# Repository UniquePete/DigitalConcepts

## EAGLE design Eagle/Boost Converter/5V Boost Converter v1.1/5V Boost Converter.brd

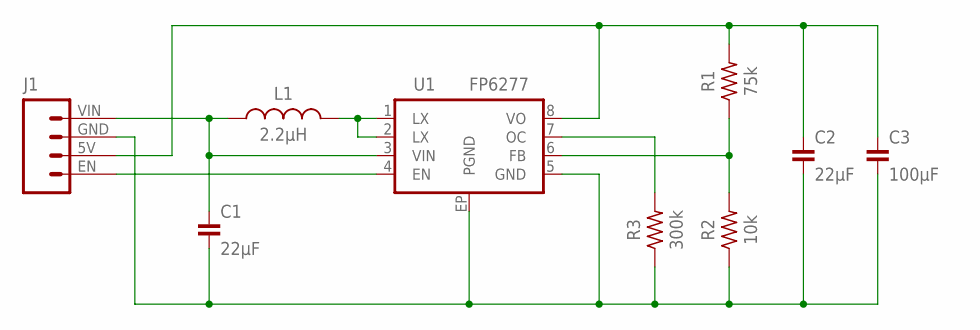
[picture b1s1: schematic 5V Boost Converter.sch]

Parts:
C1, C2: 22µF; C0805
C3: 100µF; C1206
J1: HEADER-1X4-FP6277; CONN_04-FP6277
L1: 2.2µH; L1008
R1: 75k; R0805
R2: 10k; R0805
R3: 300k; R0805
U1: FP6277; SOP-8(EP)

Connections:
5V: C2.1, C3.1, J1.5V (2), R1.2, U1.8 (VO)
EN: J1.EN (1), U1.4 (EN)
GND: C1.2, C2.2, C3.2, J1.GND (3), R2.1, R3.1, U1.5 (GND), U1.EP (PGND)
unnamed: L1.P$1 (1), U1.1 (LX), U1.2 (LX)
unnamed: R1.1, R2.2, U1.6 (FB)
unnamed: R3.2, U1.7 (OC)
VIN: C1.1, J1.VIN (4), L1.P$2 (2), U1.3 (VIN)

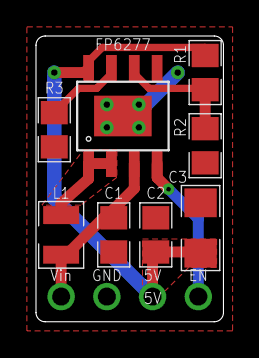
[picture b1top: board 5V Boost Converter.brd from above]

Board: 2 copper layers, 10.4 x 15.9 mm, 9 parts (1 on the bottom side), 7 nets.

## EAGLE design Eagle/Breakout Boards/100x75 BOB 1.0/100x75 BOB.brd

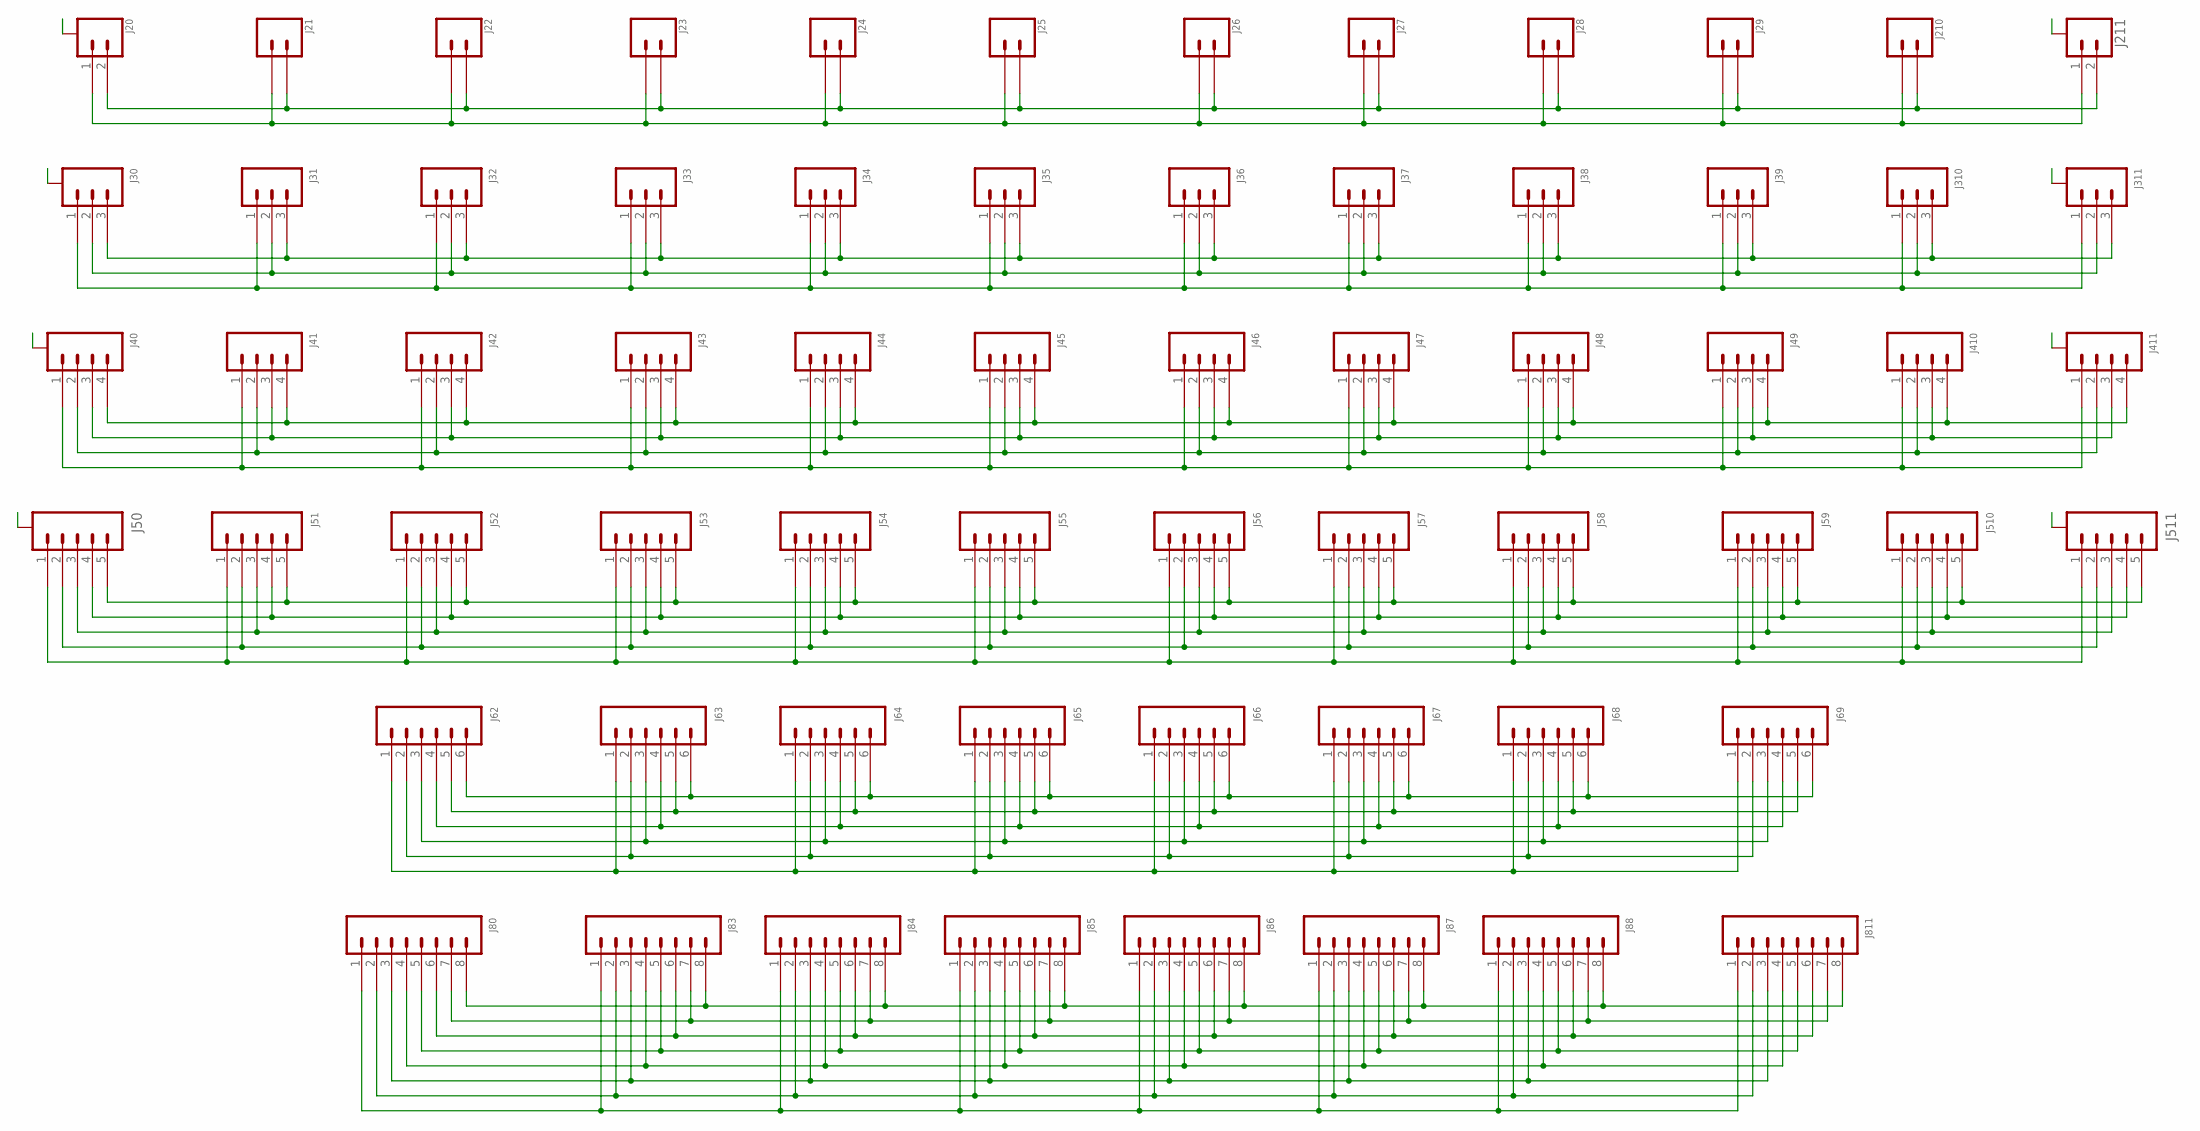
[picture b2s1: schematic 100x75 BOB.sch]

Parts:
J20, J211: JST-SH1.0-2-SMD-VERTICAL; JST-SH1.0-2-VERTICAL
J21, J210: JST-GH1.25-2-VERTICAL
J22, J29: JST-PH2.0-2-VERTICAL
J23, J24, J25, J26, J27, J28: HEADER-1X2-GENERIC; CONN_02-GENERIC
J30, J311: JST-SH1.0-3-SMD-VERTICAL; JST-SH1.0-3-VERTICAL
J31, J310: JST-GH1.25-3-VERTICAL
J32, J39: JST-PH2.0-3-VERTICAL
J33, J34, J35, J36, J37, J38: HEADER-1X3-GENERIC; CONN_03-GENERIC
J40, J411: JST-SH1.0-4-SMD-VERTICAL; JST-SH1.0-4-VERTICAL
J41, J410: JST-GH1.25-4-VERTICAL
J42, J49: JST-PH2.0-4-VERTICAL
J43, J44, J45, J46, J47, J48: HEADER-1X4-GENERIC; CONN_04-GENERIC
J50, J511: JST-SH1.0-5-SMD-VERTICAL; JST-SH1.0-5-VERTICAL
J51, J510: JST-GH1.25-5-VERTICAL
J52, J59: JST-PH2.0-5-VERTICAL
J53, J54, J55, J56, J57, J58: HEADER-1X5-GENERIC; CONN_05-GENERIC
J62, J69: RJ11-6P6C-VERTICAL; RJ11-6-VERTICAL
J63, J64, J65, J66, J67, J68: HEADER-1X6-GENERIC; CONN_06-GENERIC
J80, J811: RJ45-8P8C-VERTICAL; RJ45-VERTICAL
J83, J84, J85, J86, J87, J88: HEADER-1X8-GENERIC; CONN_08-GENERIC

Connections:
A: J20.A@1 (A), J20.A@2 (A), J30.A@1 (A), J30.A@3 (A), J40.A@1 (A), J40.A@4 (A), J50.A@1 (A), J50.A@5 (A), J211.A@1 (A), J211.A@2 (A), J311.A@1 (A), J311.A@3 (A), J411.A@1 (A), J411.A@4 (A), J511.A@1 (A), J511.A@5 (A)
unnamed: J20.1, J21.1, J22.1, J23.1, J24.1, J25.1, J26.1, J27.1, J28.1, J29.1, J210.1, J211.1
unnamed: J30.3, J31.3, J32.3, J33.3, J34.3, J35.3, J36.3, J37.3, J38.3, J39.3, J310.3, J311.3
unnamed: J30.2, J31.2, J32.2, J33.2, J34.2, J35.2, J36.2, J37.2, J38.2, J39.2, J310.2, J311.2
unnamed: J30.1, J31.1, J32.1, J33.1, J34.1, J35.1, J36.1, J37.1, J38.1, J39.1, J310.1, J311.1
unnamed: J80.8, J83.8, J84.8, J85.8, J86.8, J87.8, J88.8, J811.8
unnamed: J80.7, J83.7, J84.7, J85.7, J86.7, J87.7, J88.7, J811.7
unnamed: J20.2, J21.2, J22.2, J23.2, J24.2, J25.2, J26.2, J27.2, J28.2, J29.2, J210.2, J211.2
unnamed: J80.6, J83.6, J84.6, J85.6, J86.6, J87.6, J88.6, J811.6
unnamed: J80.5, J83.5, J84.5, J85.5, J86.5, J87.5, J88.5, J811.5
unnamed: J80.4, J83.4, J84.4, J85.4, J86.4, J87.4, J88.4, J811.4
unnamed: J80.3, J83.3, J84.3, J85.3, J86.3, J87.3, J88.3, J811.3
unnamed: J80.2, J83.2, J84.2, J85.2, J86.2, J87.2, J88.2, J811.2
unnamed: J80.1, J83.1, J84.1, J85.1, J86.1, J87.1, J88.1, J811.1
unnamed: J62.6, J63.6, J64.6, J65.6, J66.6, J67.6, J68.6, J69.6
unnamed: J62.5, J63.5, J64.5, J65.5, J66.5, J67.5, J68.5, J69.5
unnamed: J62.4, J63.4, J64.4, J65.4, J66.4, J67.4, J68.4, J69.4
unnamed: J62.3, J63.3, J64.3, J65.3, J66.3, J67.3, J68.3, J69.3
unnamed: J62.2, J63.2, J64.2, J65.2, J66.2, J67.2, J68.2, J69.2
unnamed: J62.1, J63.1, J64.1, J65.1, J66.1, J67.1, J68.1, J69.1
unnamed: J40.1, J41.1, J42.1, J43.1, J44.1, J45.1, J46.1, J47.1, J48.1, J49.1, J410.1, J411.1
unnamed: J40.2, J41.2, J42.2, J43.2, J44.2, J45.2, J46.2, J47.2, J48.2, J49.2, J410.2, J411.2
unnamed: J40.3, J41.3, J42.3, J43.3, J44.3, J45.3, J46.3, J47.3, J48.3, J49.3, J410.3, J411.3
unnamed: J40.4, J41.4, J42.4, J43.4, J44.4, J45.4, J46.4, J47.4, J48.4, J49.4, J410.4, J411.4
unnamed: J50.4, J51.4, J52.4, J53.4, J54.4, J55.4, J56.4, J57.4, J58.4, J59.4, J510.4, J511.4
unnamed: J50.3, J51.3, J52.3, J53.3, J54.3, J55.3, J56.3, J57.3, J58.3, J59.3, J510.3, J511.3
unnamed: J50.2, J51.2, J52.2, J53.2, J54.2, J55.2, J56.2, J57.2, J58.2, J59.2, J510.2, J511.2
unnamed: J50.1, J51.1, J52.1, J53.1, J54.1, J55.1, J56.1, J57.1, J58.1, J59.1, J510.1, J511.1
unnamed: J50.5, J51.5, J52.5, J53.5, J54.5, J55.5, J56.5, J57.5, J58.5, J59.5, J510.5, J511.5

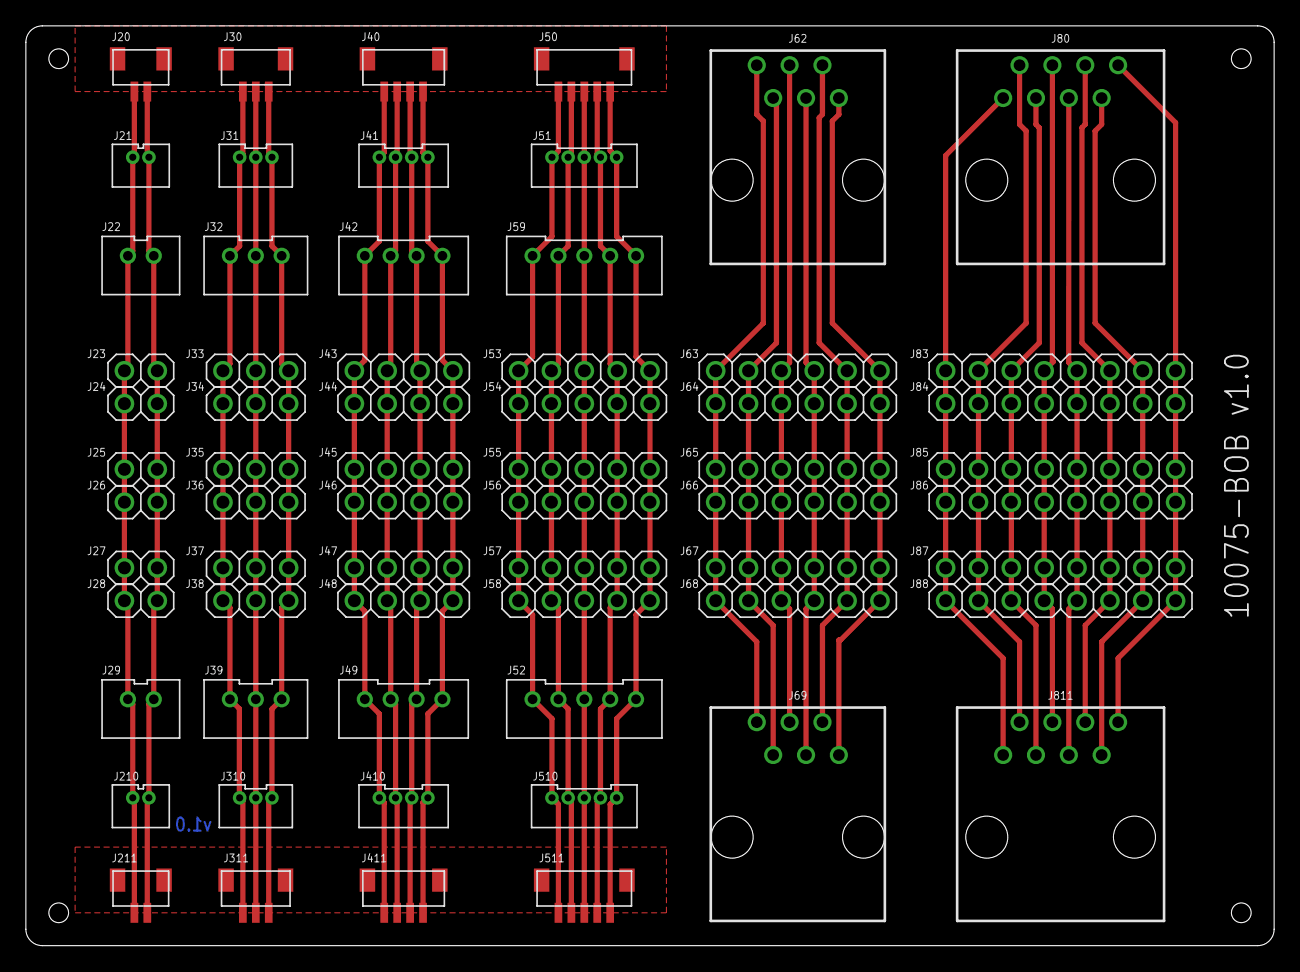
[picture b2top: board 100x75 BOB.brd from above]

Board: 2 copper layers, 96.5 x 71.1 mm, 64 parts (0 on the bottom side), 29 nets.

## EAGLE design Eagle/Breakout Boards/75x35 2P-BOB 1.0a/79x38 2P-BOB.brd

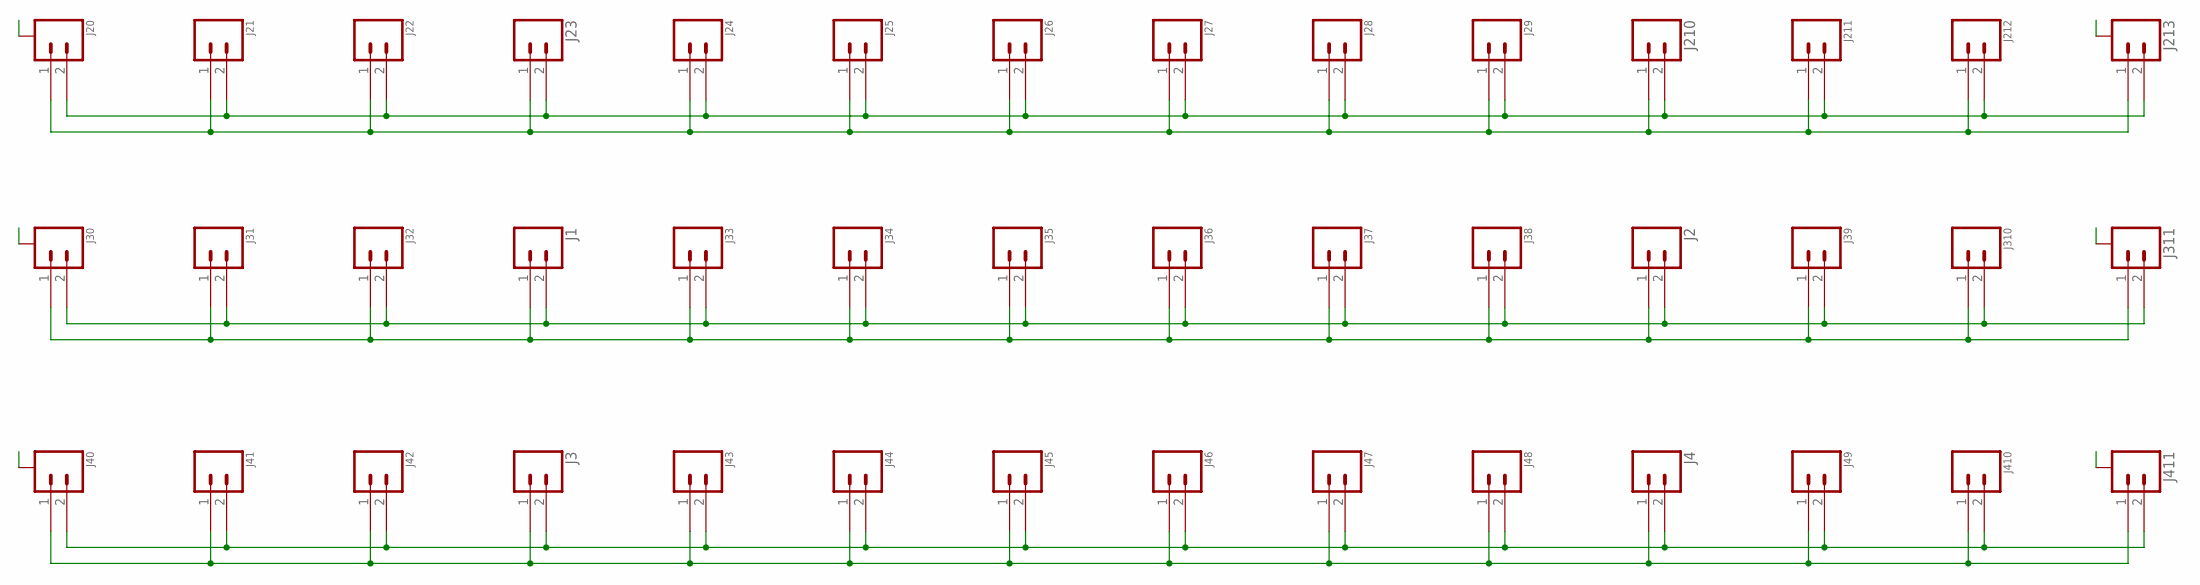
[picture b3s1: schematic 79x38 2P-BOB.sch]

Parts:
J1, J2, J3, J4, J23, J210: JST-XH2.54-2-VERTICAL; JST-XH2.4-2-VERTICAL
J20, J30, J40, J213, J311, J411: JST-SH1.0-2-SMD-VERTICAL; JST-SH1.0-2-VERTICAL
J21, J31, J41, J212, J310, J410: JST-GH1.25-2-VERTICAL
J22, J32, J39, J42, J49, J211: JST-PH2.0-2-VERTICAL
J24, J25, J26, J27, J28, J29, J33, J34, J35, J36, J37, J38, J43, J44, J45, J46, J47, J48: HEADER-1X2-GENERIC; CONN_02-GENERIC

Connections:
A: J20.A@1 (A), J20.A@2 (A), J30.A@1 (A), J30.A@2 (A), J40.A@1 (A), J40.A@2 (A), J213.A@1 (A), J213.A@2 (A), J311.A@1 (A), J311.A@2 (A), J411.A@1 (A), J411.A@2 (A)
unnamed: J20.1, J21.1, J22.1, J23.1, J24.1, J25.1, J26.1, J27.1, J28.1, J29.1, J210.1, J211.1, J212.1, J213.1
unnamed: J1.2, J2.2, J30.2, J31.2, J32.2, J33.2, J34.2, J35.2, J36.2, J37.2, J38.2, J39.2, J310.2, J311.2
unnamed: J1.1, J2.1, J30.1, J31.1, J32.1, J33.1, J34.1, J35.1, J36.1, J37.1, J38.1, J39.1, J310.1, J311.1
unnamed: J3.2, J4.2, J40.2, J41.2, J42.2, J43.2, J44.2, J45.2, J46.2, J47.2, J48.2, J49.2, J410.2, J411.2
unnamed: J3.1, J4.1, J40.1, J41.1, J42.1, J43.1, J44.1, J45.1, J46.1, J47.1, J48.1, J49.1, J410.1, J411.1
unnamed: J20.2, J21.2, J22.2, J23.2, J24.2, J25.2, J26.2, J27.2, J28.2, J29.2, J210.2, J211.2, J212.2, J213.2

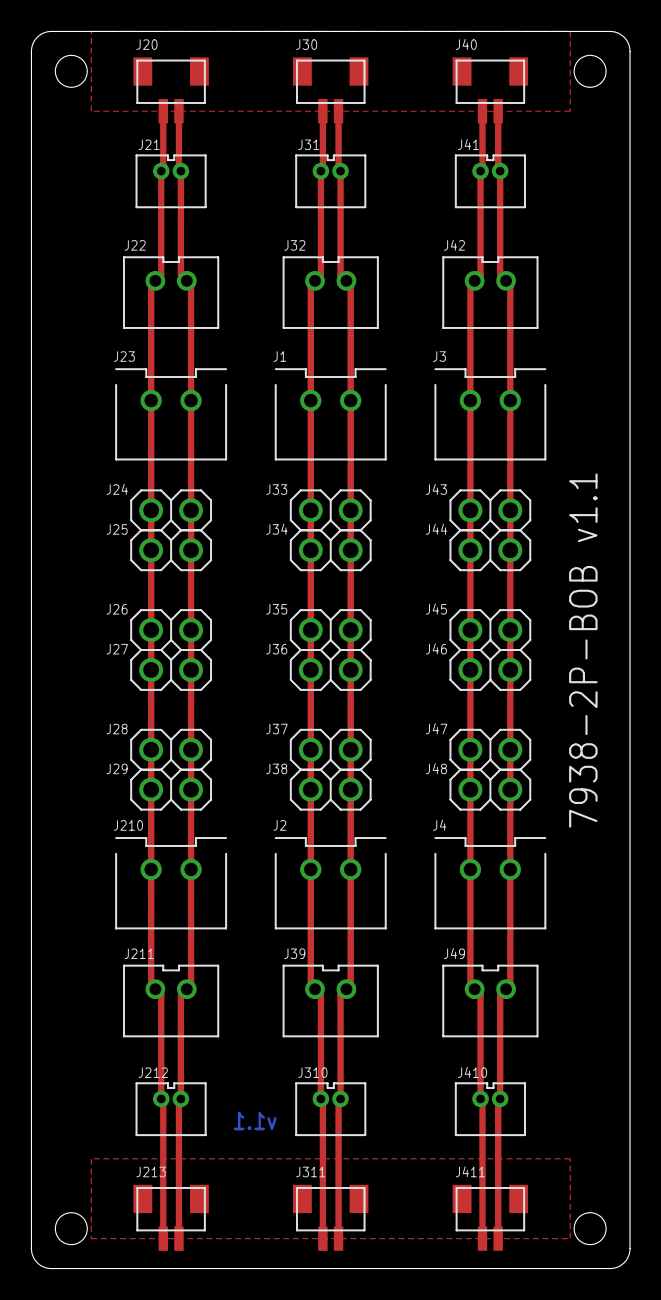
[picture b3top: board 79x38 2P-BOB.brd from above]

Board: 2 copper layers, 38.1 x 78.7 mm, 42 parts (0 on the bottom side), 7 nets.

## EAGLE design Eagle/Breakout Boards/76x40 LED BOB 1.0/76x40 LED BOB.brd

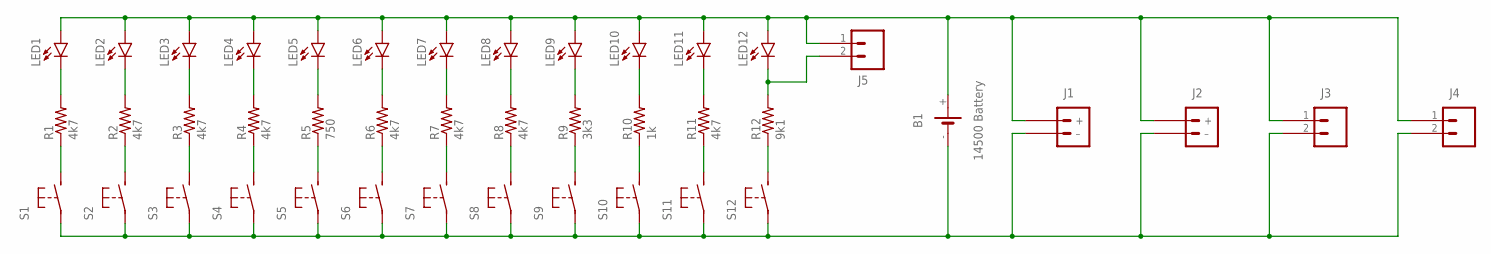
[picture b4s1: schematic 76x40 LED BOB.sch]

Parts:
B1: 14500 Battery; BATTERY-14500
J1: JST-PH2.0-2-H-POWER; JST-PH2.0-2-HORIZONTAL-POWER
J2: JST-GH1.25-2-HORIZONTAL-POWER; JST-GH1.25-2-HORIZONTAL
J3, J4, J5: HEADER-1X2-GENERIC; CONN_02-GENERIC
LED1, LED2, LED3, LED4, LED5, LED6, LED7, LED8, LED9, LED10, LED11, LED12: LEDCHIP-LED0805; CHIP-LED0805
R1, R2, R3, R4, R6, R7, R8, R11: 4k7; R0805
R5: 750; R0805
R9: 3k3; R0805
R10: 1k; R0805
R12: 9k1; R0805
S1, S2, S3, S4, S5, S6, S7, S8, S9, S10, S11, S12: SWITCH-MOMENTARY-2-PIN; SWITCH-2-PAD

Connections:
unnamed: LED1.C, R1.2
unnamed: R1.1, S1.P$2 (S)
unnamed: J5.2, LED12.C, R12.2
unnamed: LED2.C, R2.2
unnamed: R2.1, S2.P$2 (S)
unnamed: LED3.C, R3.2
unnamed: R3.1, S3.P$2 (S)
unnamed: LED4.C, R4.2
unnamed: R4.1, S4.P$2 (S)
unnamed: LED5.C, R5.2
unnamed: R5.1, S5.P$2 (S)
unnamed: LED6.C, R6.2
unnamed: R6.1, S6.P$2 (S)
unnamed: LED7.C, R7.2
unnamed: R7.1, S7.P$2 (S)
unnamed: LED8.C, R8.2
unnamed: R8.1, S8.P$2 (S)
unnamed: LED9.C, R9.2
unnamed: R9.1, S9.P$2 (S)
unnamed: LED10.C, R10.2
unnamed: R10.1, S10.P$2 (S)
unnamed: LED11.C, R11.2
unnamed: R11.1, S11.P$2 (S)
unnamed: R12.1, S12.P$2 (S)
unnamed: B1.+, J1.+, J2.+, J3.1, J4.1, J5.1, LED1.A, LED2.A, LED3.A, LED4.A, LED5.A, LED6.A, LED7.A, LED8.A, LED9.A, LED10.A, LED11.A, LED12.A
unnamed: B1.-, J1.- (–), J2.- (–), J3.2, J4.2, S1.P$1, S2.P$1, S3.P$1, S4.P$1, S5.P$1, S6.P$1, S7.P$1, S8.P$1, S9.P$1, S10.P$1, S11.P$1, S12.P$1

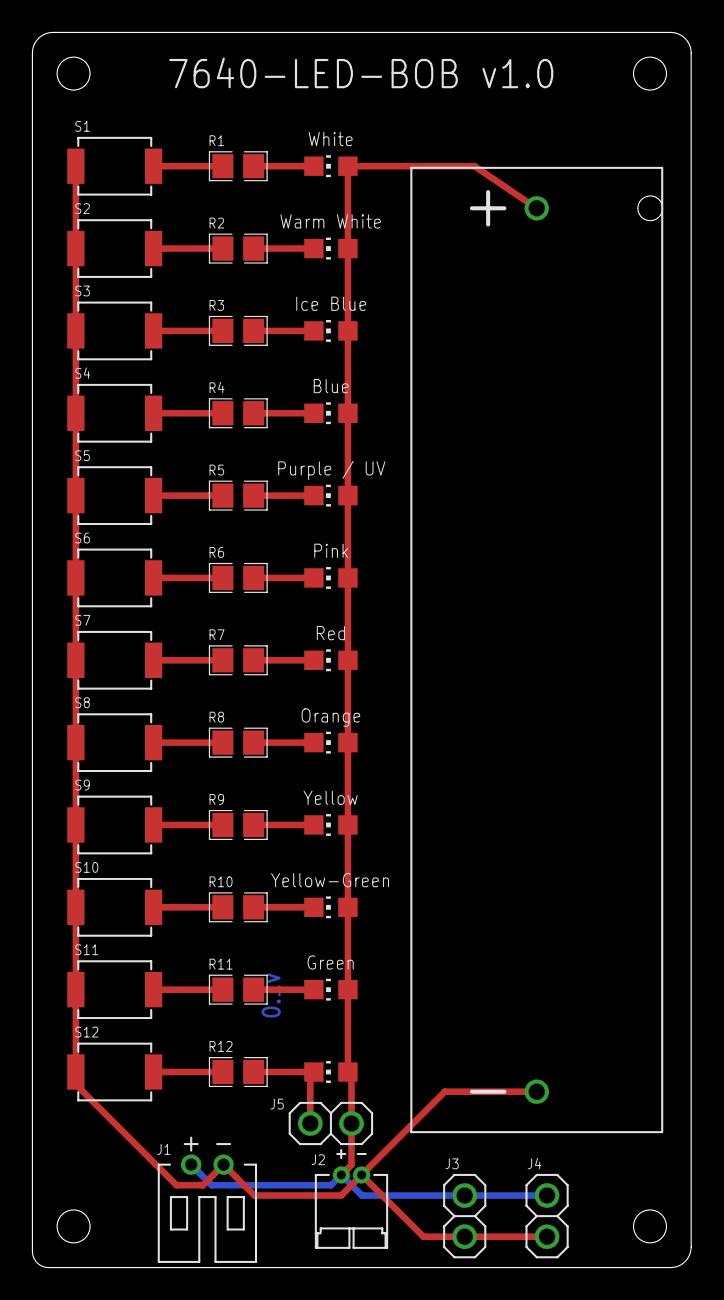
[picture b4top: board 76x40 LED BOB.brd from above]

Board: 2 copper layers, 40.6 x 76.2 mm, 42 parts (0 on the bottom side), 26 nets.

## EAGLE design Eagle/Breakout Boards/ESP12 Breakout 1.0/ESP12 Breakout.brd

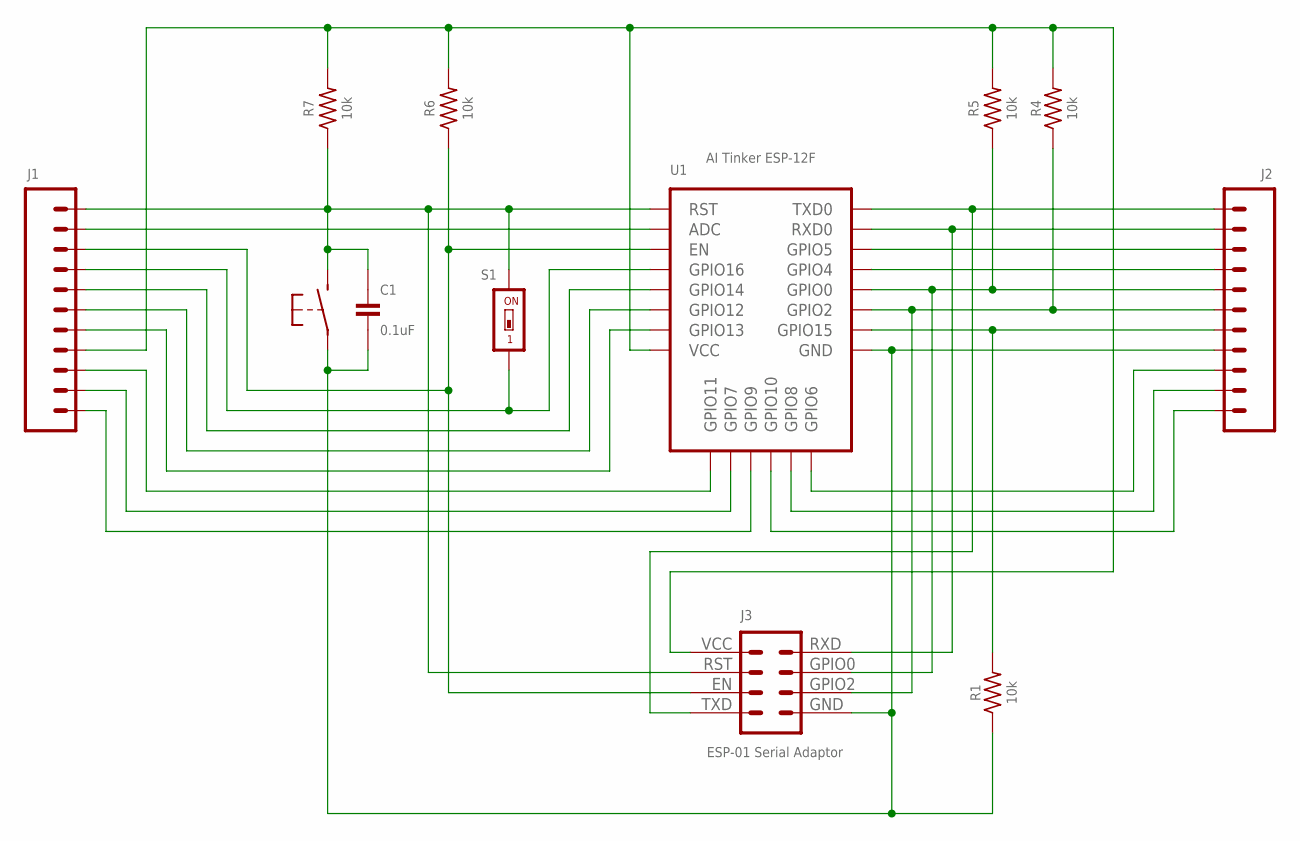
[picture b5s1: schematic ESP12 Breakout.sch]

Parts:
C1: 0.1uF; C0805
J1, J2: HEADER-1X11-GENERIC; CONN_11-GENERIC
J3: ESP-01 Serial Adaptor; CONN_2X4-ESP-01-SERIAL
R1, R4: 10k; R0805-VIA-2
R5, R6, R7: 10k; R0805
S1: Wake; SMD-001
S2: SWITCH-MOMENTARY-2-PIN; SWITCH-2-PAD
U1: AI Tinker ESP-12F; ESP-12E/F

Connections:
GND: C1.2, J2.4, J3.GND (1), R1.1, S2.P$1, U1.GND
unnamed: J1.1, U1.GPIO9
unnamed: J2.5, R1.2, R1.2@VIA (2), U1.GPIO15
unnamed: J1.7, U1.GPIO14
unnamed: C1.1, J1.11, J3.RST (6), R7.1, S1.2, S2.P$2 (S), U1.RST
unnamed: J1.6, U1.GPIO12
unnamed: J1.5, U1.GPIO13
unnamed: J1.10, U1.ADC
unnamed: J1.9, J3.EN (7), R6.1, U1.EN
unnamed: J2.9, U1.GPIO5
unnamed: J2.11, J3.TXD (8), U1.TXD0
unnamed: J2.6, J3.GPIO2 (2), R4.1, U1.GPIO2
unnamed: J2.8, U1.GPIO4
unnamed: J2.7, J3.GPIO0 (3), R5.1, U1.GPIO0
unnamed: J2.1, U1.GPIO10
unnamed: J2.10, J3.RXD (4), U1.RXD0
unnamed: J2.3, U1.SCLK (GPIO6)
unnamed: J1.8, S1.1, U1.GPIO16
unnamed: J2.2, U1.MOSI (GPIO8)
unnamed: J1.3, U1.CS0 (GPIO11)
unnamed: J1.2, U1.MISO (GPIO7)
VCC: J1.4, J3.VCC (5), R4.2, R4.2@VIA (2), R5.2, R6.2, R7.2, U1.VCC

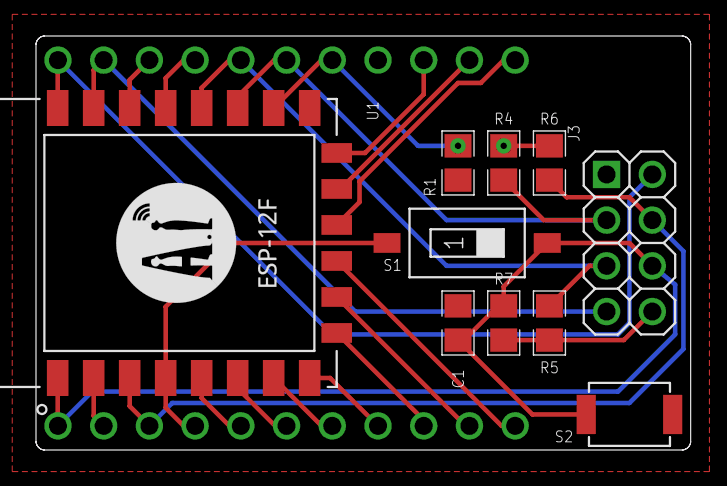
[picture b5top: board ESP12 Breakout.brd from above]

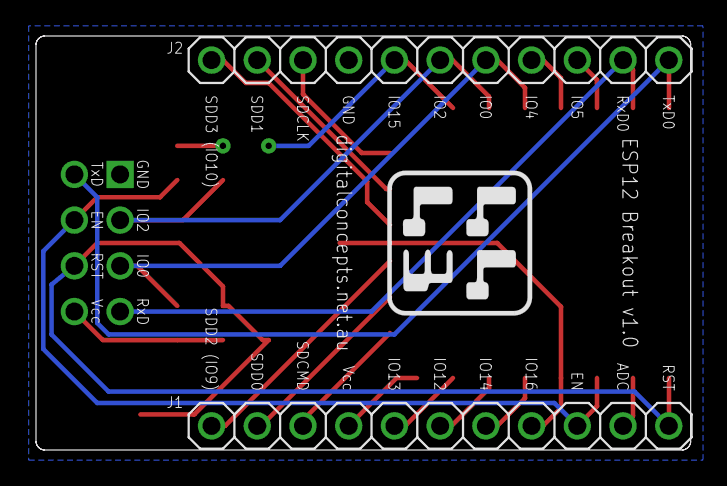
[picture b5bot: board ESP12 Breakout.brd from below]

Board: 2 copper layers, 36.4 x 23.0 mm, 12 parts (2 on the bottom side), 22 nets.
